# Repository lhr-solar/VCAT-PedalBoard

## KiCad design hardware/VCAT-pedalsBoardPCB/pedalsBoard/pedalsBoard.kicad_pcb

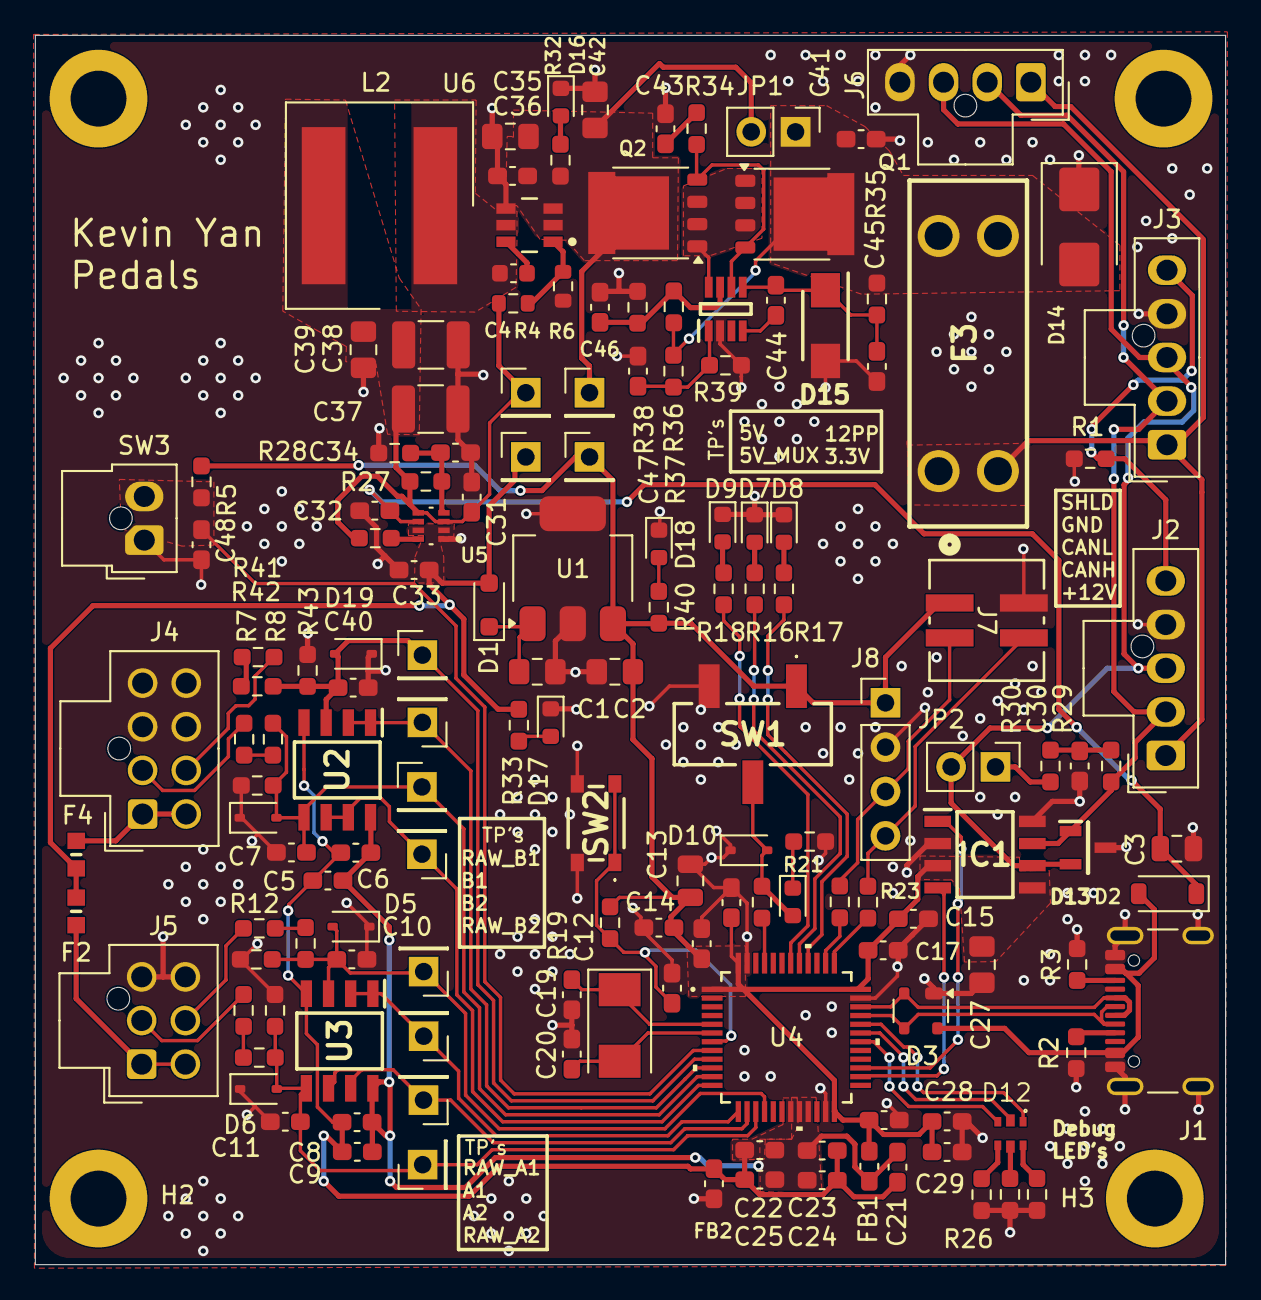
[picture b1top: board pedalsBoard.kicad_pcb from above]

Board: 2 copper layers, 68.2 x 70.4 mm, 156 parts (0 on the bottom side), 79 nets.

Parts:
C1, C2, C27, C42: 10u; C_0805_2012Metric_Pad1.18x1.45mm_HandSolder
C3: 10u; C_0805_2012Metric
C4: 100n; C_0603_1608Metric
C5, C7, C8, C10, C11, C40: .1u; C_0603_1608Metric_Pad1.08x0.95mm_HandSolder
C6, C9: 10u; C_0603_1608Metric_Pad1.08x0.95mm_HandSolder
C12, C14, C15, C16, C17, C18, C22, C23, C26, C31, C32, C33, C34: 0.1uF; C_0603_1608Metric_Pad1.08x0.95mm_HandSolder
C13: 10uF; C_0805_2012Metric
C19, C20: 26p; C_0603_1608Metric_Pad1.08x0.95mm_HandSolder
C21: 100nF; C_0603_1608Metric_Pad1.08x0.95mm_HandSolder
C24, C25: 1uF; C_0603_1608Metric_Pad1.08x0.95mm_HandSolder
C28, C29, C30, C41, C46, C47: 0.1u; C_0603_1608Metric_Pad1.08x0.95mm_HandSolder
C35: 4.7u; C_0805_2012Metric_Pad1.18x1.45mm_HandSolder
C36: 100n; C_0603_1608Metric_Pad1.08x0.95mm_HandSolder
C37, C38: 22u; C_1210_3225Metric_Pad1.33x2.70mm_HandSolder
C39: 3.3u; C_0805_2012Metric_Pad1.18x1.45mm_HandSolder
C43: 10n; C_0603_1608Metric_Pad1.08x0.95mm_HandSolder
C44: 220n; C_0603_1608Metric_Pad1.08x0.95mm_HandSolder
C45: 1u; C_0603_1608Metric_Pad1.08x0.95mm_HandSolder
C48: .47u; C_0603_1608Metric_Pad1.08x0.95mm_HandSolder
D1: SBA130CH-AU_R1_000A1; D_SOD-323_HandSoldering
D2: D_Schottky; D_SOD-123
D3: SP0503BAHT; SOT-143
D4, D5, D6, D10, D19: TVS; D_SOD-323
D7, D8, D9, D11, D16, D17, D18: LED; LED_0603_1608Metric
D12: RGB_LED
D13: CDSOT23-T24CAN
D14: SMBJ15CA; D_SMB
D15: SMAF4758A; SODFL5026X125N
F2, F4: Fuse; FUSC1607X85N
F3: 1A; Fuse-3557-2
FB1, FB2: FerriteBead; C_0603_1608Metric_Pad1.08x0.95mm_HandSolder
H1, H2, H3, H4: MountingHole_Pad; MountingHole_3.2mm_M3_DIN965_Pad
IC1: TCAN3413DR
IC2: LM74502DDFR
J1: USB_C_Receptacle_USB2.0_16P; USB_C_Receptacle_GCT_USB4105-xx-A_16P_TopMnt_Horizontal
J2, J3: CAN_NANO_01x05; Molex_Nano-Fit_105309-xx05_1x05_P2.50mm_Vertical
J4: Conn_02x04_Counter_Clockwise; Molex_Nano-Fit_105310-xx08_2x04_P2.50mm_Vertical
J5: Conn_02x03_Counter_Clockwise; Molex_Nano-Fit_105310-xx06_2x03_P2.50mm_Vertical
J6: DEBUG_CAN; Molex_Nano-Fit_105309-xx04_1x04_P2.50mm_Vertical
J7: SWD_Header; SWD_Conn
J8: SWD; PinHeader_1x04_P2.54mm_Vertical
JP1: SolderJumper_2_Open; PinHeader_1x02_P2.54mm_Vertical
JP2: TRM; PinHeader_1x02_P2.54mm_Vertical
L2: 8.2u; 74439369082
Q1, Q2: PSMN012-100YS; LFPAK56
R1: 0; R_0603_1608Metric_Pad0.98x0.95mm_HandSolder
R2, R3, R8, R11, R14, R42: 5.1k; R_0603_1608Metric_Pad0.98x0.95mm_HandSolder
R4: 100k; R_0603_1608Metric
R5, R9, R12, R15, R19, R20, R31, R35, R43: 10k; R_0603_1608Metric_Pad0.98x0.95mm_HandSolder
R6: 19.1k; R_0603_1608Metric
R7, R10, R13, R41: 150; R_0603_1608Metric_Pad0.98x0.95mm_HandSolder
R16, R17, R18, R21, R24, R25, R26, R32, R33, R40: 1k; R_0603_1608Metric_Pad0.98x0.95mm_HandSolder
R22, R23: 22; R_0603_1608Metric_Pad0.98x0.95mm_HandSolder
R27: 16k; R_0603_1608Metric_Pad0.98x0.95mm_HandSolder
R28: 4.7K; R_0603_1608Metric_Pad0.98x0.95mm_HandSolder
R29, R30: 60; R_0603_1608Metric_Pad0.98x0.95mm_HandSolder
R34: 33; R_0603_1608Metric_Pad0.98x0.95mm_HandSolder
R36, R37: 100k; R_0603_1608Metric_Pad0.98x0.95mm_HandSolder
R38: 7.32k; R_0603_1608Metric_Pad0.98x0.95mm_HandSolder
R39: 15.8k; R_0603_1608Metric_Pad0.98x0.95mm_HandSolder
SW1: SW_SPDT; BootSW
SW2: Reset; TL3365AF180QG
SW3: SW_CONN; Molex_Nano-Fit_105309-xx02_1x02_P2.50mm_Vertical
TP3: TP_BSENS2_IN; PinHeader_1x01_P2.54mm_Vertical
TP4: TP_BSENS1_OUT; PinHeader_1x01_P2.54mm_Vertical
TP5: TP_BSENS2_OUT; PinHeader_1x01_P2.54mm_Vertical
TP6: TP_ACCPOT1_IN; PinHeader_1x01_P2.54mm_Vertical
TP7: TP_ACCPOT1_OUT; PinHeader_1x01_P2.54mm_Vertical
TP8: TP_ACCPOT2_IN; PinHeader_1x01_P2.54mm_Vertical
TP9: TP_ACCPOT2_OUT; PinHeader_1x01_P2.54mm_Vertical
TP10: TP_12V; PinHeader_1x01_P2.54mm_Vertical
TP11: TP_5V_VIN1; PinHeader_1x01_P2.54mm_Vertical
TP12: TP_5V_MUX; PinHeader_1x01_P2.54mm_Vertical
TP14: TP_BSENS1_IN; PinHeader_1x01_P2.54mm_Vertical
TP_3.3V1: 3.3V; PinHeader_1x01_P2.54mm_Vertical
U1: MCP1826S; SOT-223-3_TabPin2
U2, U3: Opamp_Dual; SOIC127P600X175-8N
U4: STM32G473CETx; 48PinMCU
U5: TPS2117DRLR
U6: LMR51635XDDCR; DDC0006A-MFG
Y1: Crystal; Crystal_SMD_Abracon_ABM3-2Pin_5.0x3.2mm

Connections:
+3.3V: C2.2, C12.1, C13.1, C14.1, C15.1, C16.1, C17.1, C18.1, C27.1, C28.1, C29.1, FB1.1, IC1.3 (VCC), IC1.5 (SHDNV_IO), J7.1, J8.1, R5.2, R19.2, R40.1, SW1.1 (A), TP_3.3V1.1 (1_1), U1.3 (VO), U4.1 (VBAT), U4.24 (VDD), U4.36 (VDD), U4.48 (VDD)
+5V: C33.1, D1.2 (A), F2.2, F4.2, R33.1, TP12.1 (1_1), U5.2 (VOUT), U5.7 (VOUT__1)
+5V_USB: C3.2, C32.1, D2.1 (K), U5.6 (VIN2)
+12V: F3.2, J2.1 (12V), J3.1 (12V), J6.1 (12V)
+12V_PP: C35.1, C36.1, C42.1, JP1.2 (B), Q2.5, R32.1, TP10.1 (1_1), U6.2 (EN), U6.3 (VIN)
/<NO NET>: J2.5 (SHIELD), J3.5 (SHIELD), R1.2
/ACCEL1_OUT: J5.5, R10.2
/ACCEL2_OUT: J5.2, R13.2
/B_SENS1_OUT: J4.7, R41.2
/B_SENS2_OUT: J4.2, R7.2
/CAN_H: D13.1 (CAN_H), IC1.7 (CANH), J2.2 (CAN_H), J3.2 (CAN_H), J6.2 (CAN_H), R29.1
/CAN_L: D13.2 (CAN_L), IC1.6 (CANL), J2.3 (CAN_L), J3.3 (CAN_L), J6.3 (CAN_L), JP2.2 (B)
/CAN_Transceiver/CAN_RX: IC1.4 (RXD), U4.26 (PB12)
/CAN_Transceiver/CAN_TX: IC1.1 (TXD), U4.27 (PB13)
/MCU/48PinMCU/BOOT0: R20.1, U4.45 (PB8-BOOT0)
/MCU/48PinMCU/NRST: C26.1, R19.1, SW2.1, U4.7 (PG10-NRST)
/MCU/48PinMCU/PA8: D12.5, U4.30 (PA8)
/MCU/48PinMCU/PA9: D12.3, U4.31 (PA9)
/MCU/48PinMCU/PA10: D12.1, U4.32 (PA10)
/MCU/48PinMCU/PB3: R17.1, U4.40 (PB3)
/MCU/48PinMCU/PB4: R16.1, U4.41 (PB4)
/MCU/48PinMCU/PB5: R18.1, U4.42 (PB5)
/MCU/48PinMCU/SWCLK: R22.1, U4.38 (PA14)
/MCU/48PinMCU/SWDIO: R23.1, U4.37 (PA13)
/MCU/ACCPOT_1: TP7.1 (1_1), U3.1, U3.2 (-), U4.13 (PA5)
/MCU/ACCPOT_2: TP9.1 (1_1), U3.6 (-), U3.7, U4.14 (PA6)
/MCU/B_SENS_1: TP4.1 (1_1), U2.1, U2.2 (-), U4.10 (PA2-GPIO_GREEN)
/MCU/B_SENS_2: TP5.1 (1_1), U2.6 (-), U2.7, U4.12 (PA4)
/MCU/B_SWITCH: C48.1, R5.1, SW3.2, U4.8 (PA0-GPIO_BLUE)
/MCU/RAW_ACCEL1: C10.1, D5.2 (A2), R11.1, R12.2, TP6.1 (1_1), U3.3 (+), U4.16 (PB0)
/MCU/RAW_ACCEL2: C11.1, D6.2 (A2), R14.1, R15.2, TP8.1 (1_1), U3.5 (+), U4.15 (PA7)
/MCU/RAW_BSENS1: C40.1, D19.2 (A2), R42.1, R43.2, TP14.1 (1_1), U2.3 (+), U4.9 (PA1_GPIO_RED)
/MCU/RAW_BSENS2: C7.1, D4.2 (A2), R8.1, R9.2, TP3.1 (1_1), U2.5 (+), U4.11 (PA3)
/MCU/USB-C_Connector/CC1: J1.A5 (CC1), R2.2
/MCU/USB-C_Connector/CC2: J1.B5 (CC2), R3.2
/MCU/USB-C_Connector/VBUS_IN: D2.2 (A), D3.4 (K), J1.A4 (VBUS), J1.A9 (VBUS), J1.B4 (VBUS), J1.B9 (VBUS)
/MCU/USB_D+: D3.2 (K), J1.A6 (D+), J1.B6 (D+), U4.34 (PA12)
/MCU/USB_D-: D3.3 (K), J1.A7 (D-), J1.B7 (D-), U4.33 (PA11)
/Power/12VBuck/CB: C4.1, U6.6 (CB)
/Power/12VBuck/FB: R4.2, R6.1, U6.1 (FB)
/Power/12VBuck/SW: C4.2, L2.1, U6.5 (SW)
/Power/12VBuck/V_out_5V: C31.1, C37.1, C38.1, C39.1, L2.2, R4.1, R27.1, R31.1, TP11.1 (1_1), U5.3 (VIN1), U5.5 (MODE)
/Power/PP/EN/UVLO: C47.1, IC2.1 (EN/UVLO), R37.2, R39.2
/Power/PP/OV: C46.1, IC2.7 (OV), R36.2, R38.1
/Power/PP/Vin: C41.1, D14.2 (A2), F3.1, JP1.1 (A), Q1.5, R35.2, R36.1, R37.1
/Power/PP/gate: IC2.6 (GATE), Q1.4, Q2.4, R34.2
/Power/PP/source: IC2.8 (SRC), Q1.1, Q1.2, Q1.3, Q2.1, Q2.2, Q2.3
/Power/Power_Mux/PR1: C34.1, R27.2, R28.1, U5.4 (PR1)
GND: C1.1, C2.1, C3.1, C7.2, C10.2, C11.2, C12.2, C13.2, C14.2, C15.2, C16.2, C17.2, C18.2, C19.1, C20.2, C26.2, C27.2, C28.2, C29.2, C30.1, C31.2, C32.2, C33.2, C34.2, C35.2, C36.2, C37.2, C38.2, C39.2, C40.2, C41.2, C42.2, C43.2, C45.1, C46.2, C47.2, C48.2, D3.1 (A), D4.1 (A1), D5.1 (A1), D6.1 (A1), D7.1 (K), D8.1 (K), D9.1 (K), D10.1 (A1), D13.3 (GND), D14.1 (A1), D15.2 (A), D16.1 (K), D17.1 (K), D18.1 (K), D19.1 (A1), FB2.2, IC1.2 (GND), IC1.8 (STB), IC2.2 (GND), J1.A1 (GND), J1.A12 (GND), J1.B1 (GND), J1.B12 (GND), J1.S1 (SHIELD), J1.S2 (Shield), J1.S3 (Shield), J1.S4 (Shield), J2.4 (GND), J3.4 (GND), J4.3, J4.4, J4.5, J4.6, J5.3, J5.4, J6.4 (GND), J7.2, J8.2, R1.1, R2.1, R3.1, R6.2, R9.1, R12.1, R15.1, R21.2, R24.2, R25.2, R26.2, R28.2, R38.2, R39.1, R43.1, SW1.3 (C), SW2.2, SW3.1, U1.2 (GND), U4.23 (VSS), U4.35 (VSS), U4.47 (VSS), U5.1 (GND), U6.4 (GND)
GNDA: C5.1, C6.1, C8.1, C9.1, C21.2, C22.2, C23.2, C24.2, C25.2, FB2.1, U2.4 (V-), U3.4 (V-), U4.19 (VSSA)
unnamed: C30.2, R29.2, R30.1
unnamed: C43.1, R34.1
unnamed: C1.2, D1.1 (K), U1.1 (VI)
unnamed: D7.2 (A), R16.2
unnamed: D8.2 (A), R17.2
unnamed: D9.2 (A), R18.2
unnamed: D10.2 (A2), D11.2 (A), R20.2, SW1.2 (B)
unnamed: D11.1 (K), R21.1
unnamed: D12.2, R24.1
unnamed: D12.4, R25.1
unnamed: D12.6, R26.1
unnamed: C44.1, C45.2, D15.1 (K), IC2.5 (VS), R35.1
unnamed: D16.2 (A), R32.2
unnamed: D17.2 (A), R33.2
unnamed: D18.2 (A), R40.2
unnamed: C44.2, IC2.4 (VCAP)
unnamed: F4.1, J4.1, J4.8
unnamed: F2.1, J5.1, J5.6
unnamed: J7.3, J8.3, R22.2
unnamed: J7.4, J8.4, R23.2
unnamed: JP2.1 (A), R30.2
unnamed: R7.1, R8.2
unnamed: R10.1, R11.2
unnamed: R13.1, R14.2
unnamed: R41.1, R42.2
unnamed: C19.2, U4.5 (PF0-OSC_IN), Y1.1
unnamed: C20.1, U4.6 (PF1-OSC_OUT), Y1.2
unnamed: R31.2, U5.8 (ST)
VDDA: C5.2, C6.2, C8.2, C9.2, C21.1, C22.1, C23.1, C24.1, C25.1, FB1.2, U2.8 (V+), U3.8 (V+), U4.20 (VREF+), U4.21 (VDDA)
